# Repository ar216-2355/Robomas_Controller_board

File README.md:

ロボマスを１６台同時に駆動できる基板（２４台までやろうと思えば動かせる）

stm32 cube ide の G474_robomas_controller パッケージ と合わせて使う想定

ロータリーエンコーダー搭載（タイマーのencoder機能は使えない）

ボタン８個のプルアップを忘れた

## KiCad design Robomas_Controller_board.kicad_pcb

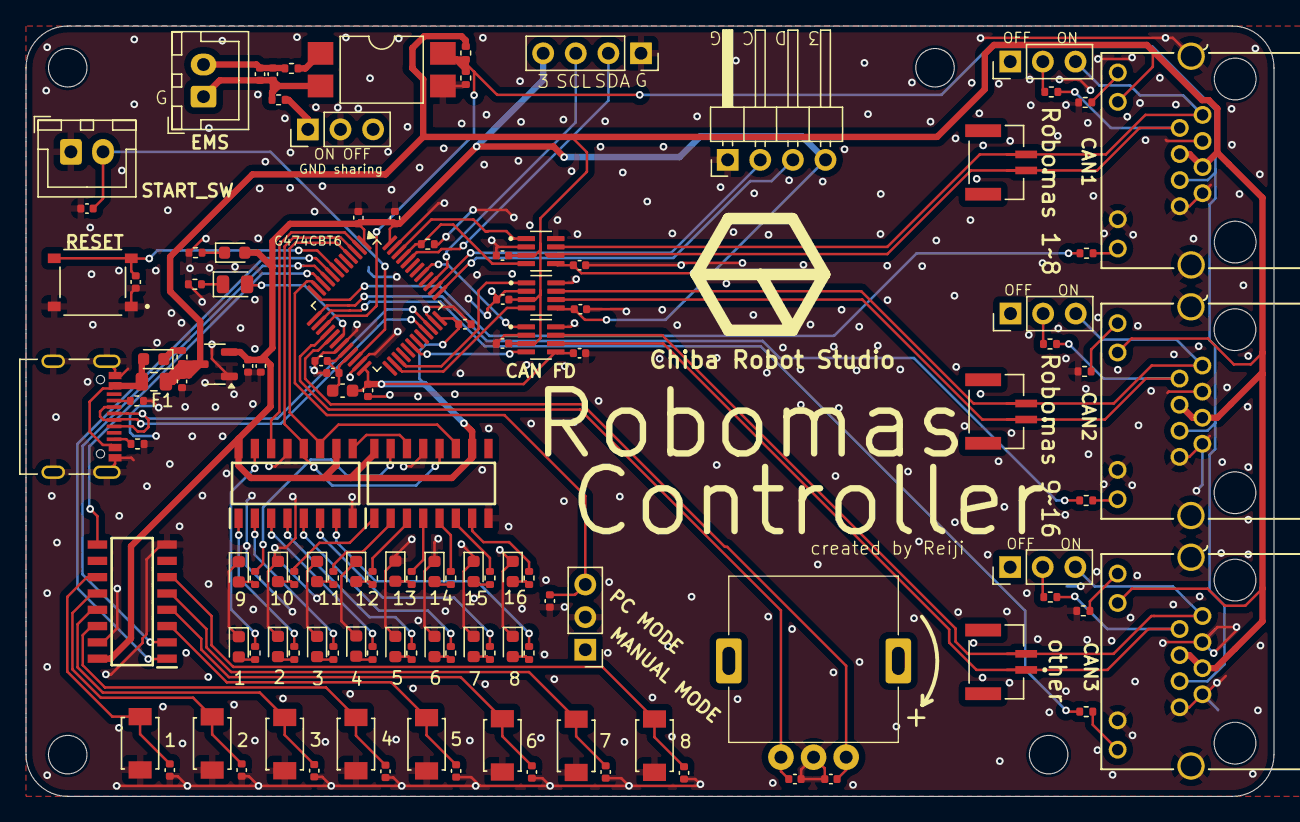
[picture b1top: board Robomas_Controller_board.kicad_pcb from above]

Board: 2 copper layers, 97.2 x 60.0 mm, 121 parts (0 on the bottom side), 98 nets.

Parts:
C1, C2, C3, C4, C7, C11, C13, C14, C15, C16, C17, C18, C19, C20, C21, C22, C23, C24, C25, C26, C27, C30: 100n; C_0402_1005Metric
C5, C8, C9, C10: 1u; C_0402_1005Metric
C6: 4.7u; C_0402_1005Metric
C12: 1n; C_0402_1005Metric
C28, C29: 10n; C_0402_1005Metric
D1, D2, D3, D4, D5, D6, D7, D8, D9, D10, D11, D12, D13, D14, D15, D16, D19: Yellow; LED_0603_1608Metric
D17: Red; LED_0603_1608Metric
D18: Green; LED_0805_2012Metric
F1: Polyfuse; Fuse_0805_2012Metric
FB1: FerriteBead_Small; C_0603_1608Metric
IC1, IC2: 74HC595D; SOIC127P600X175-16N
J1, J2, J3: RJ45_LED_Shielded; RJ45_LAN_port
J4: Conn_01x04_Pin; PinHeader_1x04_P2.54mm_Horizontal
J5: Conn_01x04_Socket; PinSocket_1x04_P2.54mm_Vertical
J6, J16: Conn_01x02_Socket; JST_XH_B2B-XH-A_1x02_P2.50mm_Vertical
J7, J8, J9, J10, J15: Conn_01x03_Pin; PinHeader_1x03_P2.54mm_Vertical
J11: 10155435-00011LF; AMPHENOL_10155435-00011LF
J12, J13, J14: Conn_01x02_Pin; JST_BM02B-GHS-TBT_LF__SN_
R1, R2: 5.1k; R_0402_1005Metric
R3, R6, R7, R8: 1.5k; R_0402_1005Metric
R4: 0; R_0402_1005Metric
R5, R28: 10k; R_0402_1005Metric
R9, R10, R11, R12, R13, R14, R15, R16, R17, R18, R19, R20, R21, R22, R23, R24, R30, R31, R32: 1k; R_0402_1005Metric
R25, R26, R27: 120; R_0402_1005Metric
R29: 20k; R_0402_1005Metric
R33: 470k; R_0402_1005Metric
R34: 470; R_0402_1005Metric
R35: 100; R_0402_1005Metric
SW1: SW_Push; SW_TS-1187A-B-A-B
SW2, SW3, SW4, SW5, SW6, SW7, SW8, SW9: SW_Push; SW_TS-1088-AR02016
SW10: RotaryEncoder; rotary_encoder
U1: STM32G474CBTx; LQFP-48_7x7mm_P0.5mm
U2: LTV-817S; SMDIP-4_W9.53mm
U3: XC6206PxxxMR; SOT-23-3
U4: 74HC165D; SOIC127P600X175-16N
U5, U6, U7: TCAN1044VDDFRQ1; SOT65P280X110-8N

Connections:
3.3V: C1.1, C2.1, C3.1, C6.1, C8.1, C10.1, C22.1, C24.1, C26.1, D17.2 (A), FB1.1, IC1.10 (~MR), IC1.16 (VCC), IC2.10 (~MR), IC2.16 (VCC), J4.4, J5.4, U1.1 (VBAT), U1.24 (VDD), U1.36 (VDD), U1.48 (VDD), U3.2 (VO), U4.16 (VCC), U5.5 (VIO/NC), U6.5 (VIO/NC), U7.5 (VIO/NC)
5V: C9.1, C21.1, C23.1, C25.1, F1.2, J1.4, J1.5, J1.10, J2.4, J2.5, J2.10, J3.4, J3.5, J3.10, R28.2, R35.1, U3.3 (VI), U5.3 (VCC), U6.3 (VCC), U7.3 (VCC)
A_conne: C28.1, SW10.A, U1.16 (PB0)
B_conne: C29.1, SW10.B, U1.17 (PB1)
CAN1_LED: R30.2, U1.12 (PA4)
CAN1_RX: R5.1, U1.45 (PB8), U5.4 (RXD)
CAN1_TX: U1.46 (PB9), U5.1 (TXD)
CAN2_LED: R31.2, U1.13 (PA5)
CAN2_RX: U1.26 (PB12), U6.4 (RXD)
CAN2_TX: U1.27 (PB13), U6.1 (TXD)
CAN3_LED: R32.2, U1.14 (PA6)
CAN3_RX: U1.30 (PA8), U7.4 (RXD)
CAN3_TX: U1.41 (PB4), U7.1 (TXD)
EMS: J1.6, J2.6, J3.6, R28.1, R29.2, U1.15 (PA7), U2.4
GND: C1.2, C2.2, C3.2, C4.2, C5.2, C6.2, C7.2, C8.2, C9.2, C10.2, C13.1, C14.1, C15.1, C16.1, C17.1, C18.1, C19.1, C20.1, C21.2, C22.2, C23.2, C24.2, C25.2, C26.2, C27.2, C28.2, C29.2, C30.2, D1.1 (K), D2.1 (K), D3.1 (K), D4.1 (K), D5.1 (K), D6.1 (K), D7.1 (K), D8.1 (K), D9.1 (K), D10.1 (K), D11.1 (K), D12.1 (K), D13.1 (K), D14.1 (K), D15.1 (K), D16.1 (K), IC1.8 (GND), IC1.13 (~OE), IC2.8 (GND), IC2.13 (~OE), J1.3, J1.7, J1.8, J1.11, J1.SH, J2.3, J2.7, J2.8, J2.11, J2.SH, J3.3, J3.7, J3.8, J3.11, J3.SH, J4.1, J5.1, J7.2, J11.A1_B12 (GND), J11.B1_A12 (GND), J11.SH1 (SHIELD), J11.SH2 (SHIELD), J11.SH3 (SHIELD), J11.SH4 (SHIELD), J15.2, J16.1, R1.2, R2.1, R5.2, R6.2, R7.2, R8.2, R29.1, R33.2, R34.2, SW1.1, SW2.1, SW3.1, SW4.1, SW5.1, SW6.1, SW7.1, SW8.1, SW9.1, SW10.C, U1.19 (VSSA), U1.23 (VSS), U1.35 (VSS), U1.47 (VSS), U2.3, U3.1 (GND), U4.8 (GND), U4.15 (~CE), U5.2 (GND), U5.8 (STB), U6.2 (GND), U6.8 (STB), U7.2 (GND), U7.8 (STB)
I2C_SCL: J5.3, U1.39 (PA15)
I2C_SDA: J5.2, U1.44 (PB7)
unnamed: D1.2 (A), R9.2
unnamed: D2.2 (A), R10.2
unnamed: D3.2 (A), R11.2
unnamed: D4.2 (A), R12.2
unnamed: D5.2 (A), R13.2
unnamed: D6.2 (A), R14.2
unnamed: D7.2 (A), R15.2
unnamed: D8.2 (A), R16.2
unnamed: D9.2 (A), R17.2
unnamed: D10.2 (A), R18.2
unnamed: D11.2 (A), R19.2
unnamed: D12.2 (A), R20.2
unnamed: D13.2 (A), R21.2
unnamed: D14.2 (A), R22.2
unnamed: D15.2 (A), R23.2
unnamed: D16.2 (A), R24.2
unnamed: D17.1 (K), R33.1
unnamed: D18.2 (A), U1.18 (PB2)
unnamed: D18.1 (K), R34.1
unnamed: D19.1 (K), R35.2
unnamed: IC1.15 (Q0), R9.1
unnamed: IC1.1 (Q1), R10.1
unnamed: IC1.2 (Q2), R11.1
unnamed: IC1.3 (Q3), R12.1
unnamed: IC1.4 (Q4), R13.1
unnamed: IC1.5 (Q5), R14.1
unnamed: IC1.6 (Q6), R15.1
unnamed: IC1.7 (Q7), R16.1
unnamed: IC1.9 (Q7S), IC2.14 (DS)
unnamed: IC2.15 (Q0), R17.1
unnamed: IC2.1 (Q1), R18.1
unnamed: IC2.2 (Q2), R19.1
unnamed: IC2.3 (Q3), R20.1
unnamed: IC2.4 (Q4), R21.1
unnamed: IC2.5 (Q5), R22.1
unnamed: IC2.6 (Q6), R23.1
unnamed: IC2.7 (Q7), R24.1
unnamed: J1.12, R30.1
unnamed: J1.9, R6.1
unnamed: J2.12, R31.1
unnamed: J2.9, R7.1
unnamed: J3.12, R32.1
unnamed: J3.9, R8.1
unnamed: C11.2, C12.2, J6.1, R4.1, U2.2
unnamed: C11.1, C12.1, J6.2, R3.1
unnamed: J7.1, R4.2
unnamed: J8.2, R25.2
unnamed: J9.2, R26.2
unnamed: J10.2, R27.2
unnamed: J3.1, J10.3, J14.1, U7.7 (CANH)
unnamed: J11.A5 (CC1), R2.2
unnamed: J11.B5 (CC2), R1.1
unnamed: J1.1, J8.3, J12.1, U5.7 (CANH)
unnamed: J1.2, J12.2, R25.1, U5.6 (CANL)
unnamed: J2.1, J9.3, J13.1, U6.7 (CANH)
unnamed: J2.2, J13.2, R26.1, U6.6 (CANL)
unnamed: J3.2, J14.2, R27.1, U7.6 (CANL)
unnamed: C27.1, J15.3, U1.11 (PA3)
unnamed: R3.2, U2.1
unnamed: C7.1, SW1.2, U1.7 (PG10)
unnamed: C4.1, C5.1, FB1.2, U1.20 (VREF+), U1.21 (VDDA)
unnamed: C13.2, SW2.2, U4.11 (D0)
unnamed: C14.2, SW3.2, U4.12 (D1)
unnamed: C15.2, SW4.2, U4.13 (D2)
unnamed: C16.2, SW5.2, U4.14 (D3)
unnamed: C17.2, SW6.2, U4.3 (D4)
unnamed: C18.2, SW7.2, U4.4 (D5)
unnamed: C19.2, SW8.2, U4.5 (D6)
unnamed: C20.2, SW9.2, U4.6 (D7)
RCLK: IC1.12 (STCP), IC2.12 (STCP), U1.3 (PC14)
SER: IC1.14 (DS), U1.2 (PC13)
SRCLK: IC1.11 (SHCP), IC2.11 (SHCP), U1.4 (PC15)
SWCLK: J4.2, U1.38 (PA14)
SWDIO: J4.3, U1.37 (PA13)
SW_ClockPulse: U1.9 (PA1), U4.2 (CP)
SW_Output7: U1.10 (PA2), U4.9 (Q7)
SW_ParallelLoad: U1.8 (PA0), U4.1 (~PL)
Start_button: C30.1, J16.2, U1.22 (PB10)
USB_DM: J11.A7 (DN1), J11.B7 (DN2), U1.33 (PA11)
USB_DP: J11.A6 (DP1), J11.B6 (DP2), U1.34 (PA12)
VBUS: D19.2 (A), F1.1, J11.A4_B9 (VBUS), J11.B4_A9 (VBUS)

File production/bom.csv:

Designator,Footprint,Quantity,Value,LCSC Part #
"C1, C11, C13, C14, C15, C16, C17, C18, C19, C2, C20, C21, C22, C23, C24, C25, C26, C27, C3, C30, C4, C7",0402,22,100n,
"C10, C5, C8, C9",0402,4,1u,
C12,0402,1,1n,
"C28, C29",0402,2,10n,
C6,0402,1,4.7u,
"D1, D10, D11, D12, D13, D14, D15, D16, D19, D2, D3, D4, D5, D6, D7, D8, D9",0603,17,Yellow,
D17,0603,1,Red,
D18,0805,1,Green,
F1,0805,1,Polyfuse,
FB1,0603,1,FerriteBead_Small,
"IC1, IC2",SOIC127P600X175-16N,2,74HC595D,
"J1, J2, J3",RJ45_LAN_port,3,RJ45_LED_Shielded,
"J10, J15, J7, J8, J9",PinHeader_1x03_P2.54mm_Vertical,5,Conn_01x03_Pin,
J11,AMPHENOL_10155435-00011LF,1,10155435-00011LF,
"J12, J13, J14",JST_BM02B-GHS-TBT_LF__SN_,3,Conn_01x02_Pin,
"J16, J6",JST_XH_B2B-XH-A_1x02_P2.50mm_Vertical,2,Conn_01x02_Socket,
J4,PinHeader_1x04_P2.54mm_Horizontal,1,Conn_01x04_Pin,
J5,PinSocket_1x04_P2.54mm_Vertical,1,Conn_01x04_Socket,
"R1, R2",0402,2,5.1k,
"R10, R11, R12, R13, R14, R15, R16, R17, R18, R19, R20, R21, R22, R23, R24, R30, R31, R32, R9",0402,19,1k,
"R25, R26, R27",0402,3,120,
"R28, R5",0402,2,10k,
R29,0402,1,20k,
"R3, R6, R7, R8",0402,4,1.5k,
R33,0402,1,470k,
R34,0402,1,470,
R35,0402,1,100,
R4,0402,1,0,
SW1,SW_TS-1187A-B-A-B,1,SW_Push,
SW10,rotary_encoder,1,RotaryEncoder,
"SW2, SW3, SW4, SW5, SW6, SW7, SW8, SW9",SW_TS-1088-AR02016,8,SW_Push,
U1,LQFP-48_7x7mm_P0.5mm,1,STM32G474CBTx,
U2,SMDIP-4_W9.53mm,1,LTV-817S,
U3,SOT-23-3,1,XC6206PxxxMR,
U4,SOIC127P600X175-16N,1,74HC165D,74HC165D
"U5, U6, U7",SOT65P280X110-8N,3,TCAN1044VDDFRQ1,

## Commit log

2026-02-04 ただの櫂經
2026-02-25 step step

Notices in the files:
parts and their libraries:
Copyright 2016 Accelerated Designs. All rights reserved.
